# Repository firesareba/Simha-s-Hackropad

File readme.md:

# Simha's Macropad RP2040

This is a custom 2x3 macropad with a rotary encoder and an OLED screen.

### Inspiration

I wanted to create a macropad that was both functional and aesthetically pleasing. I created a macropad featuring a 2x3 key matrix, a rotary encoder with a push button, and an OLED display, all powered by a **Seeed XIAO RP2040**.

### Challenges

This was my first time using Fusion 360. It was a really cool experience to learn. A lot of my friends tell me to use Onshape so I might stick with that in the future because Fusion360 was very clunky in my opinion. I was first very intimidated by having to create a entire PCB from scratch but the guide was super useful and taught me the basics of KiCad (i might make my own board one day). I big issue for me was creating the firmware, as QMK was just not complying so I went with a KMK firmware instead.

A big challenge is I could not find a accurate symbol for the schematic so I learned to make one!

THANKS HACK CLUB! 

### Specifications

**Bill of Materials (BOM):**

-   6x Cherry MX Switches
-   6x 1N4148 Diodes
-   1x Seeed XIAO RP2040
-   1x SSD1306 0.91" 128x32 I2C OLED Display
-   1x Rotary Encoder (EC11-style with switch)
-   6x Blank DSA Keycaps
-   1x Rotary Encoder Knob
-   4x M3x16 Bolt
-   4x M3 Heatset

---

****A BOM CSV is also included but doesn't account for things outside the PCB***

**Visuals:**

| Schematic | PCB | Case |
| :---: | :---: | :---: |
| ![Simha Macropad Schematic] | ![Simha Macropad PCB] | ![Simha Macropad Case] |
    |    | 

**Notes:**

I might add QMK later if it works

***3D MODELS ON COMPONENTS MAY NOT BE ACCURATE AND EXIST FOR VISUALS ONLY***

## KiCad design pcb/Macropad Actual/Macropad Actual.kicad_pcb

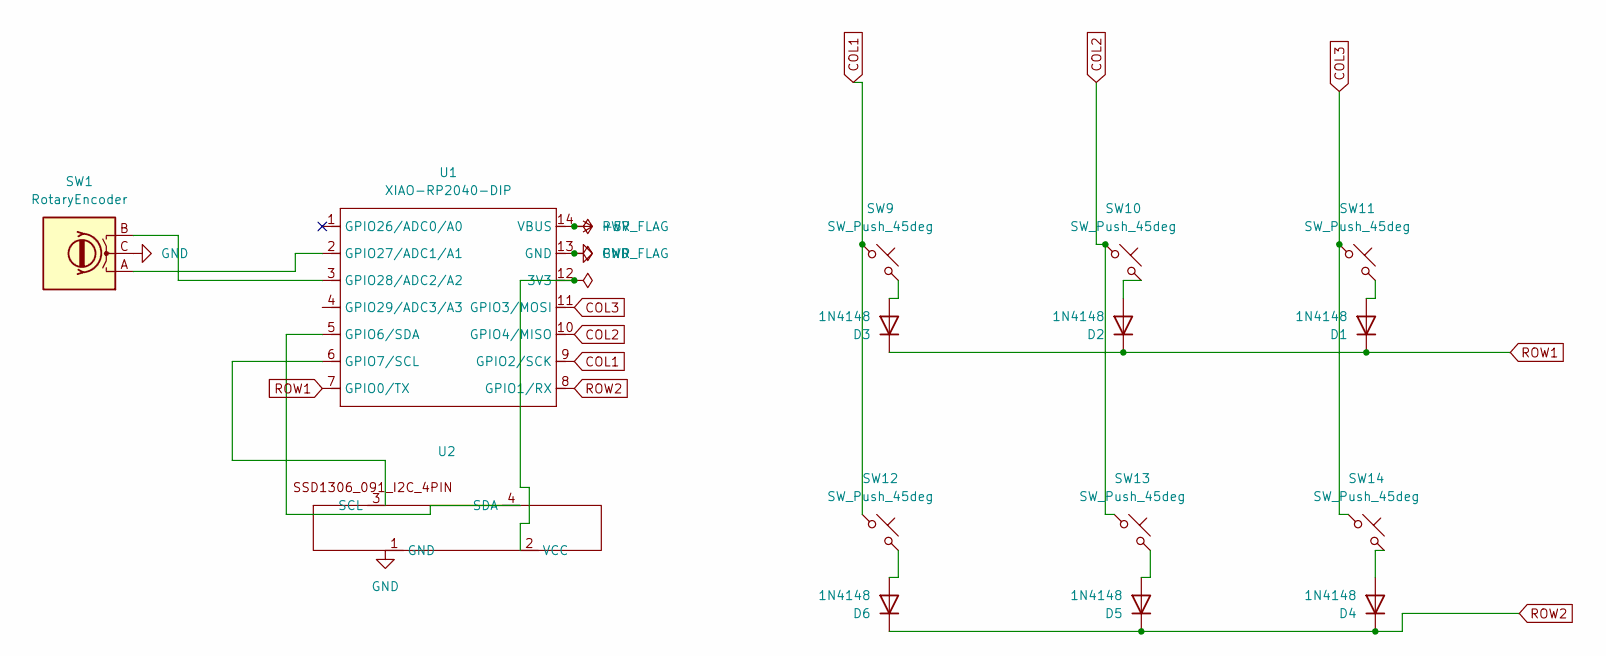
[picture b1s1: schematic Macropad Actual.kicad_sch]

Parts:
D1, D2, D3, D4, D5, D6: 1N4148; D_DO-35_SOD27_P7.62mm_Horizontal
SW1: RotaryEncoder; RotaryEncoder_Alps_EC11E-Switch_Vertical_H20mm_CircularMoun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
SW9, SW10, SW11, SW12, SW13, SW14: SW_Push_45deg; SW_Cherry_MX_1.00u_PCB
U1: XIAO-RP2040-DIP
U2: SSD1306-0.91-OLED-4pin-128x32

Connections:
+5V: U1.14 (VBUS)
COL1: SW9.1, SW12.1, U1.9 (GPIO2/SCK)
COL2: SW10.1, SW13.1, U1.10 (GPIO4/MISO)
COL3: SW11.1, SW14.1, U1.11 (GPIO3/MOSI)
GND: SW1.C, U1.13 (GND), U2.1 (GND)
unnamed: D1.2 (A), SW11.2
unnamed: D2.2 (A), SW10.2
unnamed: D3.2 (A), SW9.2
unnamed: D4.2 (A), SW14.2
unnamed: D5.2 (A), SW13.2
unnamed: D6.2 (A), SW12.2
unnamed: U1.12 (3V3), U2.2 (VCC)
unnamed: U1.5 (GPIO6/SDA), U2.4 (SDA)
unnamed: U1.6 (GPIO7/SCL), U2.3 (SCL)
unnamed: SW1.A, U1.2 (GPIO27/ADC1/A1)
unnamed: SW1.B, U1.3 (GPIO28/ADC2/A2)
ROW1: D1.1 (K), D2.1 (K), D3.1 (K), U1.7 (GPIO0/TX)
ROW2: D4.1 (K), D5.1 (K), D6.1 (K), U1.8 (GPIO1/RX)

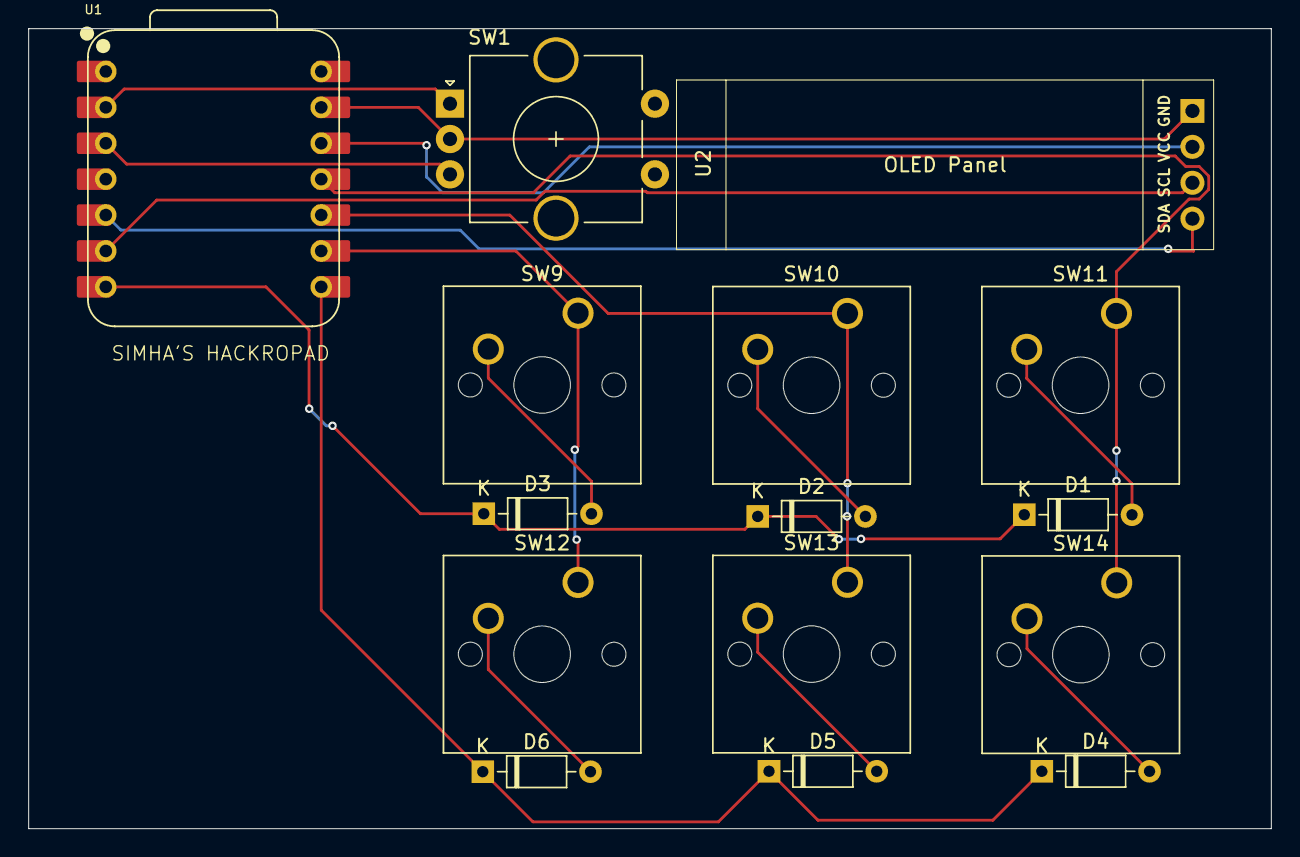
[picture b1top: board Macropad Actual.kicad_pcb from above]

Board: 2 copper layers, 87.9 x 56.6 mm, 15 parts (0 on the bottom side), 17 nets.

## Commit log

2025-11-30 Add README
2025-11-30 Rename readme.txt to readme.md
2025-11-30 Update readme with BOM CSV note
    Added note about BOM CSV not accounting for external components.
2025-11-30 Document challenge of creating schematic symbol
    Added a note about creating an accurate symbol for the schematic.
